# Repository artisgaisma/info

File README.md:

# Angle Meter 
### NO1 - BNO055 - Absolute Orientation Sensor- triaxial accelerometer, gyroscope, and magnetometer
```
Precise Orientation: The BNO055 is designed for precise orientation measurements and provides Euler angles (roll, pitch, and yaw) with three decimal places.
Integrated Sensor Fusion: The sensor fusion algorithm is implemented on the chip, reducing the complexity of fusion calculations on the microcontroller.
High Accuracy: The BNO055 is known for its high accuracy and low drift, making it suitable for applications that require precise orientation data.
Calibration: It includes an automatic calibration feature for both gyroscope and magnetometer, simplifying the calibration process.
Arduino Compatibility: There are Arduino libraries available for the BNO055, making it easy to use with Arduino projects.
```

### NO2 - MPU6050 - Inertial Measurement Unit (IMU) - accelerometer, gyroscope, and magnetometer
```which combines a 3-axis accelerometer and a 3-axis gyroscope.
While it doesn't have a built-in magnetometer, you can often integrate a
separate magnetometer module (like the HMC5883L or its successor, the QMC5883L) for better orientation accuracy
```

### NO3  - HMC5883L
```
is a three-axis digital compass module designed for low-field magnetic sensing with
a digital interface for applications such as compassing and magnetometry. It is
commonly used in electronic projects and devices where measuring the Earth's magnetic field is necessary.
```
###  ICM-20948 - most precise but better use BNO055
```
is designed to provide accurate readings of the Earth's magnetic field
it requires sensor fusion techniques. The ICM-20948 is a 9-axis sensor,
which means it includes a 3-axis accelerometer, a 3-axis gyroscope,
and a 3-axis magnetometer. By combining the data from these sensors and
applying sensor fusion algorithms, you can obtain accurate orientation
information, including roll, pitch, and yaw angles.
```

# Altitude

### NO1 - BMP388

# Other
- CDM -> diskpart -> list disk

# Restore
```
Solution #1: Restore Deleted Files from USB Drive Using CMD
1. Connect the USB flash drive to your computer.
2. Open the Start menu, type "cmd", and hit Enter on your keyboard.
3. Type "chkdsk X: /f" in the Command Prompt window and hit Enter. Just make sure to replace “X” with the letter assigned to your USB flash drive.recover deleted files from flash drive without software
4. Finally, type "ATTRIB -H -R -S /S /D X:*.*" and hit the Enter key (Again, replace “X” with the drive letter of the USB drive).recover deleted files from flash drive
5. Wait for the process to be completed.

Solution #2: Use the Restore Previous Versions Feature
1. Connect the USB flash drive to your computer.
2. Open the Start menu, type "This pc", and hit Enter on your keyboard.
3. Right-click on your USB flash drive and select "Properties".
4. Go to the "Previous Versions" tab and look at the list of available recovery options.
5. Select a previous version and click "Restore".

Solution #3: Use a Data Recovery Software 
Today we will be using the latest version of Disk Drill to recover data. It’s is one of the most popular and well-established data recovery software on the market.

Steps to recover deleted files from a USB flash drive:
1. Go to the following address and download Disk Drill: https://www.cleverfiles.com/
2. With your pen drive connected, launch Disk Drill 
3. Click the "Search for lost data" button next to it.
4. Select which files you want Disk Drill to recover and click the "Recover" button.
```

# MCU

`8MHZ - 8,000,000 cycles per second`

```int 4bytes -2`147`483`648	to 2`147`483`648 or uint32_t 4 bytes [0-4294967295]```

`EEPROM`	 write cycle typically takes 	`3.3 m`s to complete

## TI
		
|	|	I/O|		FLASH|	RAM|	BAND|
|----|----|----|----|----|
|CC1301	| 	10-30	|	32-128|	16/20|	Sub 1GHz, Wi-Fi|
|CC1350	|	10-33	|	128KB|	20KB|	Sub-1GHz, Wi-Fi, BLE|
|CC1352R|	28	|	352KB|	80KB|	Sub-1GHz AND 2.4GHz - DUAL BAND|
|CC1352P|	26	|	352KB|	80KB|	Sub-1GHz AND 2.4GHz - integrated amplifier|
|CC2640R2|	10-31	|	128KB|	20KB|	BLE 5, 2.4GHz|
|||||
||||
|CC110L| transmit|		<1.5e|	300-928MHz|
|CC115L| transmit|		<1e|	300-928MHz|
|CC1150| transmit|		<2e |	300-900MHz|
|CC1200| transceiv|		<2.5e| 	136-960MHz|
|CC1175| trannmit|		<2.5e |	136-960MHz| - 10pcs ordere - 25eur|

***CC1310 vs CC1350: Can be replacable each other.
The main advantage of the CC1352 over the CC1350 is the increased memory. 
With the increased memory you can run multiple stacks (TI15.4 and BLE). 
CC1350 can only run one stack at a time or one full stack and partially 
another for example, you can run the full TI 15.4 Stack with limited 
BLE functionality (only beaconing ad not connections)

### Atmel
```
		I/O 	FREQ	FLASH	EEPORM	RAM	PWM	USARTS
AVR128DA32		1-24	128KB	512B	16KB		3	has WatchDogTimer
Atmega 4808	27	1-20	48KB	256B	6KB	9	3	1.5
Atmega 4809	41	1-20	48KB	256B	6KB	11	4	1.5
Atmega 328p	23	1-20	32KB	1KB	2KB	6	1	1.5EUR
Atmega 32U4	26	8/16	32KB	1KB	2.5	5?	1
Atmega 1281 	54	8/16	128KB	4KB	8KB	6	2	6EUR
Atmega 2561	54	8/16	256KB	4KB	8KB	6	2
Atmega 1280	86	8/16	128KB	4KB	8KB	12	4
Atmega 2560	86	8/16	256KB	4KB	8KB	12	4
Atxmega256a3u 	64p	32	256	4KB	16KB	22	7	8eur	Allard QuadAnt taimeris

STM32F103x8	32	8-78	64KB	---	20KB	13	3	Have sample Board

SAMD21			48MHz	256KB	NO	32KB 12	

nRF52832
```
# Atmega BOD levels
- 4.3V - 100
- 2.7 - 101
- 1.8 - 110
- disabled -111
### Atmega4808/9
- MEgaCoreX - https://github.com/MCUdude/MegaCoreX
### BOD option
- Brownout detection or BOD for short lets the microcontroller sense the input voltage and shut down if the voltage goes below the brownout setting. Below is a table that shows the available BOD options:

### BOD threshold
4.3 V
4.0 V
3.7 V
3.3 V
2.9 V
2.6 V (default option)
2.1 V
1.8 V
Disabled
 
### LPC11U3x
32-bit ARM Cortex-M0 
up to 128 kB flash; 
upto 12 kB SRAM 
4 kB EEPROM
USB device
USART

## Ferrite Bead
```
A ferrite bead is a passive device that filters high frequency noise energy 
over a broad frequency range. It becomes resistive over its intended frequency
range and dissipates the noise energy in the form of heat. ... This forms
a low-pass filter network, further reducing the high frequency power supply noise.
```

## RT9193 - LDO with loadswitch

# CODE

### Data Types
```
	"32-bit CPU"
	char		1byte	-128				to 	127
	short		2bytes	-32`768 			to	32`768
	int		4bytes	-2`147`483`648			to	2`147`483`648
	long		4bytes	-2`147`483`648			to	2`147`483`648
	long long 	8bytes	-9`223`327`036`854`775`807 	to 	9`223`327`036`854`775`807
	float		4bytes	3.4E+/--38
	double		8bytes	1.7E+/--308
	long double	16bytes

	uint8_t		1 byte	[0-255]
	uint16_t	2 bytes	[0-65535]
	uint32_t	4 bytes	[0-4294967295]
	uint64_t	8 bytes	[0-18446744073709551615]
	
```

### Comparison
```
== (equal to)
!= (not equal to)
< (less than)
> (greater than)
<= (less than or equal to)
>= (greater than or equal to)
```
### Boolean Operators
```
! (logical not)
&& (logical and)
|| (logical or)
```

### Arithmetic
```
% (remainder)
* (multiplication)
+ (addition)
- (subtraction)
/ (division)
= (assignment operator)

y += x;	y = y + x;
x -= 5;	x = x - 5;
x /= y;	x = x / y;
```

### Compound Operators
```
&= (compound bitwise and)
*= (compound multiplication)
++ (increment)
+= (compound addition)
-- (decrement)
-= (compound subtraction)
/= (compound division)
^= (compound bitwise xor)
|= (compound bitwise or)
```

### Array
```
	array_1[] = array_2[] 	// tikai pieliidzina vienu elementu
	struct 1 = struct 2 	//pieliidzina visus elementus	
```
### Bitwise Operators
```
& (bitwise and)
<< (bitshift left)
>> (bitshift right)
^ (bitwise xor)
| (bitwise or)
~ (bitwise not)

	int a = 5;        // binary: 0000000000000101
	int b = a << 3;   // binary: 0000000000101000, or 40 in decimal
	int c = b >> 3;   // binary: 0000000000000101, or back to 5 like we started with

   	1 <<  0  ==    1
    	1 <<  1  ==    2
    	1 <<  2  ==    4
    	1 <<  3  ==    8
	
	int x = -16;     		// binary: 1111111111110000
 	int y = x >> 3;  		// binary: 1111111111111110
	int y = (unsigned int)x >> 3;	// binary: 0001111111111110

```
# Pointers
### print
```
void print(char* C){
	int i=0;		//var bez
	while(*(C+i)!= '/0'){ 	//var vnk C++
		printf("%c",C[i]);
		i++;//var C++
	}
	printf("/n");
}
int main(){
	char C[20] = "Hello";
	print(C);
}
```
### to Servos

```
107. rinda	#include <Servo.h>
			Servo STAB_SERVO;
			Servo WING_SERVO;
			Servo RUDD_SERVO;
			Servo HOOK_SERVO;
		/* MK edit - izveidojam poiteru matricu uz klasēm "ptr_Servo", kura glabajas objektu adreses */
		Servo* ptr_Servo[] = [ &STAB_SERVO, &WING_SERVO, &RUDD_SERVO, &HOOK_SERVO ];

203. rinda	void toParameters( uint8_t gID, uint8_t pID, float value ){
  
    			switch(gID){
        			case 1:
            				Parameters.FLY_TIME[pID] = value;
		/* MK edit - darbina servo */
		if ( pID > 4) ptr_Servo[PID]->write(value);

            				break;
				case 2:
            				Parameters.CIR[pID] = (uint8_t)value;
            				break;
```

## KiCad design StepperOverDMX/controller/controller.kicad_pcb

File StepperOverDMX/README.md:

# StepperOverDMX
A system to control a stepper motor over DMX protocol.

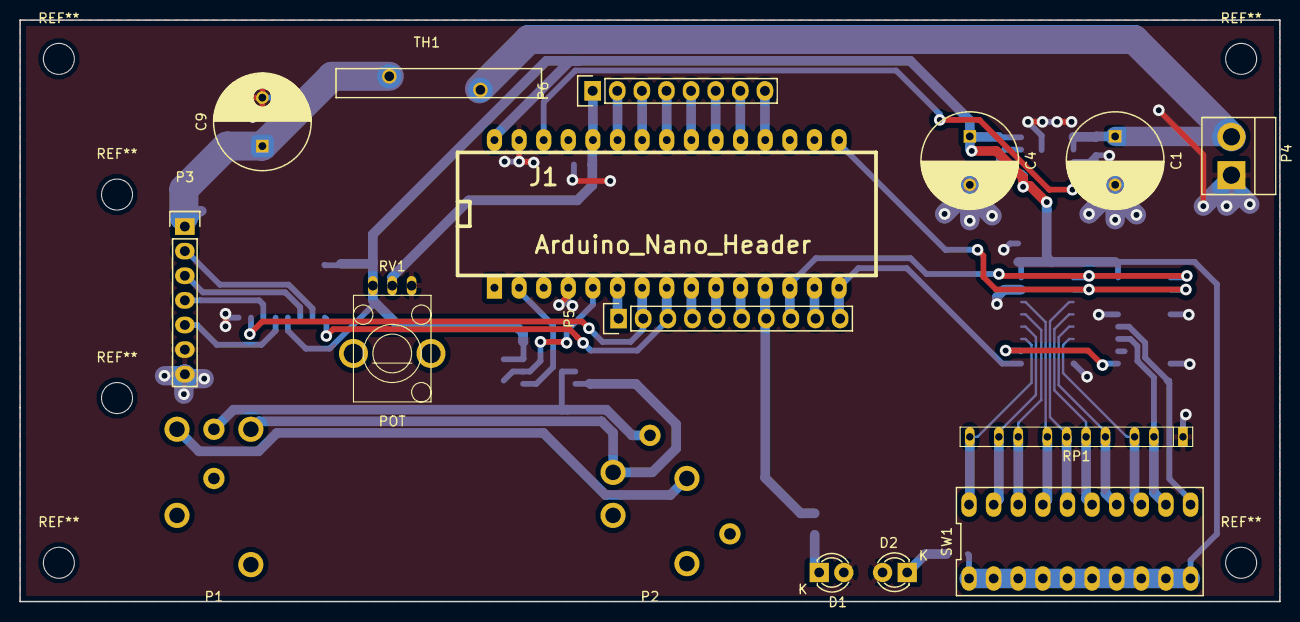
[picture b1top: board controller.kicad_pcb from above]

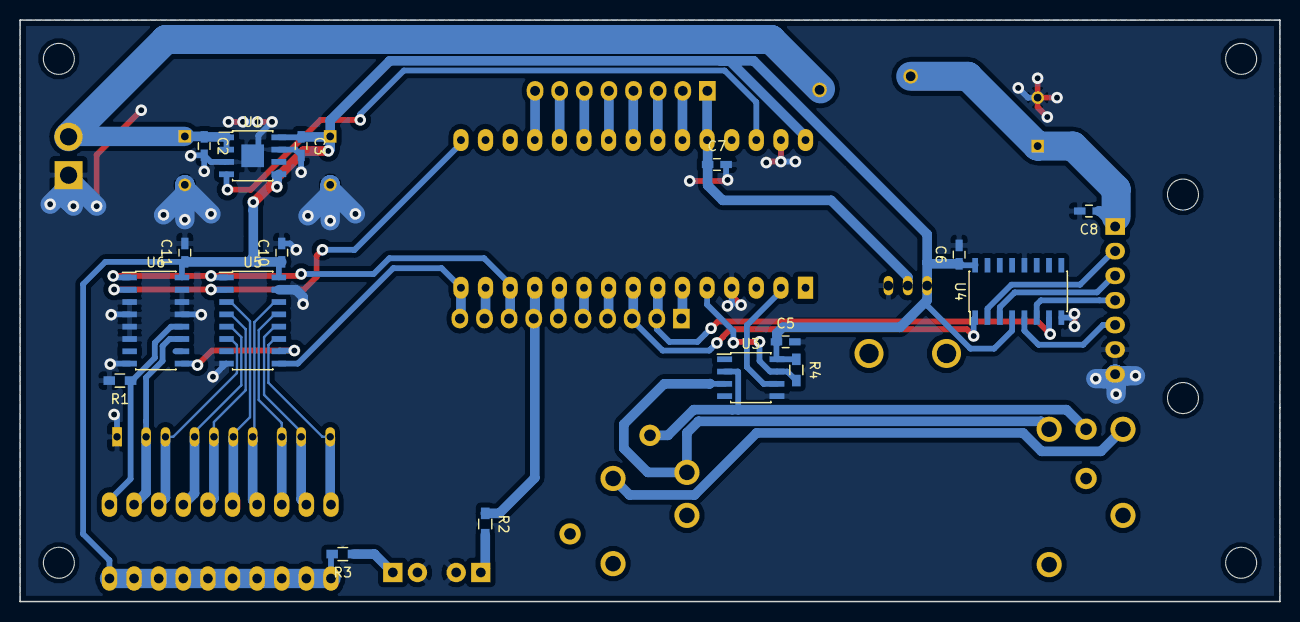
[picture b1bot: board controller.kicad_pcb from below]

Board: 2 copper layers, 130.0 x 60.0 mm, 33 parts (17 on the bottom side), 46 nets.

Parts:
C1, C4, C9: CP1; C_Radial_D10_L20_P5
C2, C3, C5, C6, C7, C8, C10, C11: 1u; C_0603_HandSoldering
D1, D2: LED; LED-3MM
J1: Arduino_Nano_Header; arduino_mini
P1: CONN_01X03; NC3MBH
P2: CONN_01X03; NC3FBH2
P3: CONN_01X07; Pin_Header_Straight_1x07
P4: CONN_01X02; Pin_Header_Straight_1x02_Pitch3.96mm_Friction_Lock
P5: CONN_01X10; Pin_Header_Straight_1x10
P6: CONN_01X08; Pin_Header_Straight_1x08
R1, R4: R; R_0603_HandSoldering
R2, R3: 330; R_0603_HandSoldering
RP1: R_PACK9_COMM; r-sil_10
RV1: POT; trimmer_alps-rk09k1130ah1
SW1: DIPS_10; A6ER-1010
TH1: THERMISTOR; MC36201
U1: MAX5024; SOIC-8-1EP_3.9x4.9mm_Pitch1.27mm
U3: IL610; SOIC-8_3.9x4.9mm_Pitch1.27mm
U4: MAX3040; SOIC-16_3.9x9.9mm_Pitch1.27mm
U5, U6: 74LS165; SOIC-16_3.9x9.9mm_Pitch1.27mm

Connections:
+5V: C3.1, C4.1, C5.1, C6.1, C10.1, C11.1, J1.30, R3.2, R4.1, RV1.3, SW1.1, SW1.2, SW1.3, SW1.4, SW1.5, SW1.6, SW1.7, SW1.8, SW1.9, SW1.10, U1.5, U1.8, U3.8, U4.4, U4.16, U5.16, U6.16
/CLOCK: J1.16, U5.2, U6.2
/DATA: J1.15, P5.10, U5.9
/DXM_OK: J1.12, P5.7, R2.1
/LATCH: J1.13, P5.8, U5.1, U6.1
/RESET: J1.28, U1.4
GND: C1.2, C2.2, C3.2, C4.2, C5.2, C6.2, C7.2, C8.2, C9.2, C10.2, C11.2, D1.2, D2.2, J1.4, J1.29, P3.6, P3.7, P4.1, R1.2, RP1.1, RV1.1, U1.3, U1.7, U1.9, U3.5, U4.8, U4.12, U5.8, U5.15, U6.3, U6.4, U6.5, U6.6, U6.8, U6.13, U6.14, U6.15
unnamed: C7.1, J1.26, P6.1, RV1.2
unnamed: C8.1, C9.1, P3.1, TH1.1
unnamed: D1.1, R2.2
unnamed: D2.1, R3.1
unnamed: J1.2, U3.6
unnamed: J1.5, R4.2, U3.7
unnamed: J1.6, P5.1
unnamed: J1.7, P5.2, U4.7
unnamed: J1.8, P5.3, U4.1
unnamed: J1.9, P5.4
unnamed: J1.10, P5.5
unnamed: J1.11, P5.6
unnamed: J1.14, P5.9
unnamed: J1.19, P6.8
unnamed: J1.20, P6.7
unnamed: J1.21, P6.6
unnamed: J1.22, P6.5
unnamed: J1.23, P6.4
unnamed: J1.24, P6.3
unnamed: J1.25, P6.2
unnamed: P1.1, P2.1
unnamed: P1.2, P2.2, U3.3
unnamed: P1.3, P2.3, U3.2
unnamed: P3.2, U4.2
unnamed: P3.3, U4.3
unnamed: P3.4, U4.6
unnamed: P3.5, U4.5
unnamed: R1.1, SW1.11, U6.12
unnamed: RP1.2, SW1.12, U6.11
unnamed: RP1.3, SW1.13, U5.6
unnamed: RP1.4, SW1.14, U5.5
unnamed: RP1.5, SW1.15, U5.4
unnamed: RP1.6, SW1.16, U5.3
unnamed: RP1.7, SW1.17, U5.14
unnamed: RP1.8, SW1.18, U5.13
unnamed: RP1.9, SW1.19, U5.12
unnamed: RP1.10, SW1.20, U5.11
unnamed: U5.10, U6.9
VCC: C1.1, C2.1, P4.2, TH1.2, U1.1, U1.2

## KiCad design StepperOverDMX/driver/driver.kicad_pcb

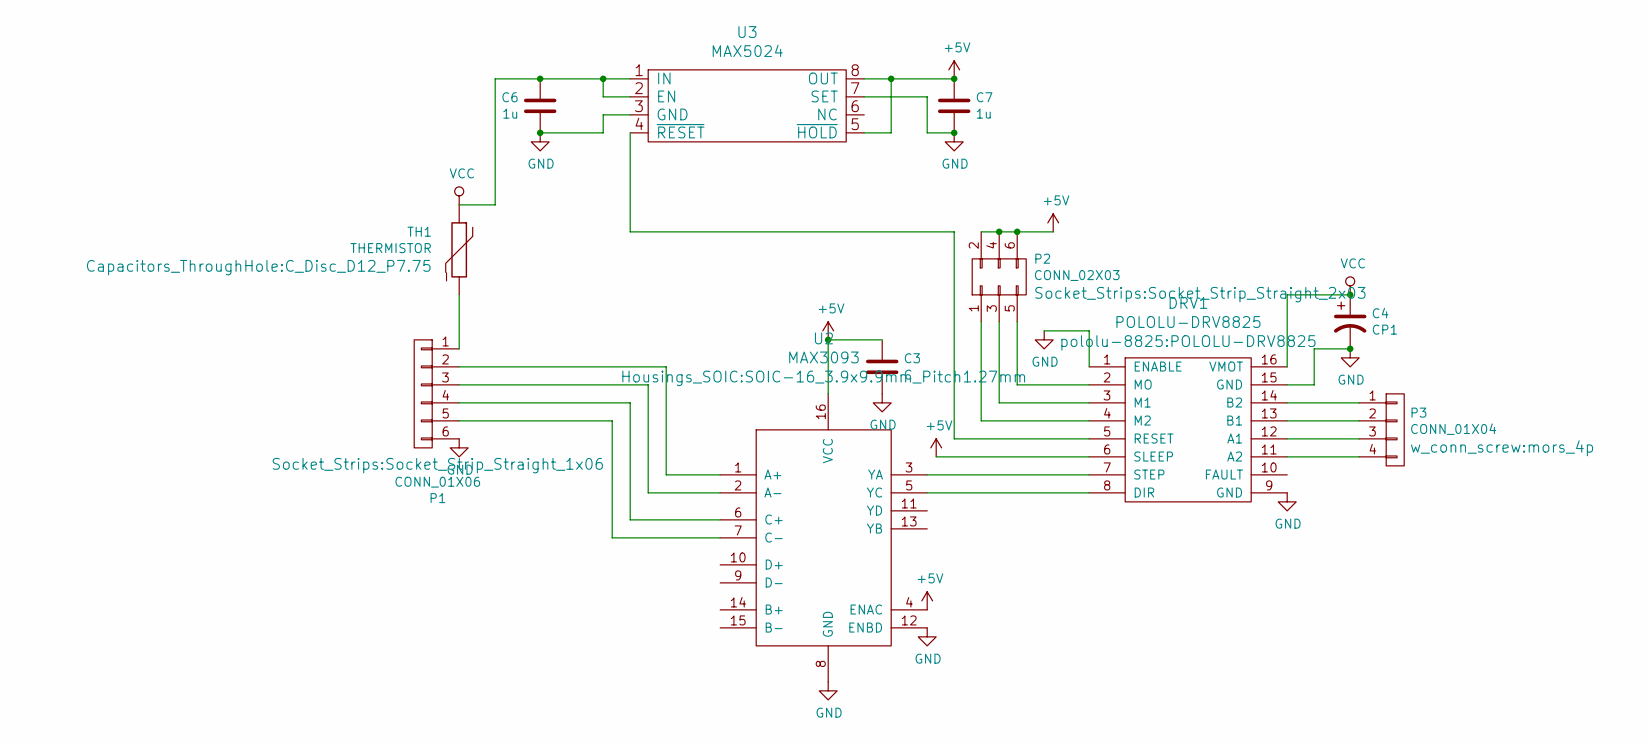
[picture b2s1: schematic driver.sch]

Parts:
C3: C; C_0603_HandSoldering
C4: CP1; C_Radial_D10_L20_P2.5
C6, C7: 1u; C_0603_HandSoldering
DRV1: POLOLU-DRV8825; PartNo ?
P1: CONN_01X06; Socket_Strip_Straight_1x06; PartNo ?
P2: CONN_02X03; Socket_Strip_Straight_2x03; PartNo ?
P3: CONN_01X04; mors_4p; PartNo ?
TH1: THERMISTOR; C_Disc_D12_P7.75; PartNo ?
U2: MAX3093; SOIC-16_3.9x9.9mm_Pitch1.27mm; PartNo ?
U3: MAX5024; SOIC-8-1EP_3.9x4.9mm_Pitch1.27mm; PartNo ?

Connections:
+5V: C3.1, C7.1, DRV1.6 (SLEEP), P2.2, P2.4, P2.6, U2.4 (ENAC), U2.16 (VCC), U3.5 (~HOLD), U3.8 (OUT)
GND: C3.2, C4.2, C6.2, C7.2, DRV1.1 (ENABLE), DRV1.9 (GND), DRV1.15 (GND), P1.6, U2.8 (GND), U2.12 (ENBD), U3.3 (GND), U3.7 (SET), U3.9
unnamed: DRV1.2 (MO), P2.5
unnamed: DRV1.3 (M1), P2.3
unnamed: DRV1.4 (M2), P2.1
unnamed: DRV1.5 (RESET), U3.4 (~RESET)
unnamed: DRV1.7 (STEP), U2.3 (YA)
unnamed: DRV1.8 (DIR), U2.5 (YC)
unnamed: DRV1.11 (A2), P3.4
unnamed: DRV1.12 (A1), P3.3
unnamed: DRV1.13 (B1), P3.2
unnamed: DRV1.14 (B2), P3.1
unnamed: P1.1, TH1.2
unnamed: P1.2, U2.1 (A+)
unnamed: P1.3, U2.2 (A-)
unnamed: P1.4, U2.6 (C+)
unnamed: P1.5, U2.7 (C-)
VCC: C4.1, C6.1, DRV1.16 (VMOT), TH1.1, U3.1 (IN), U3.2 (EN)

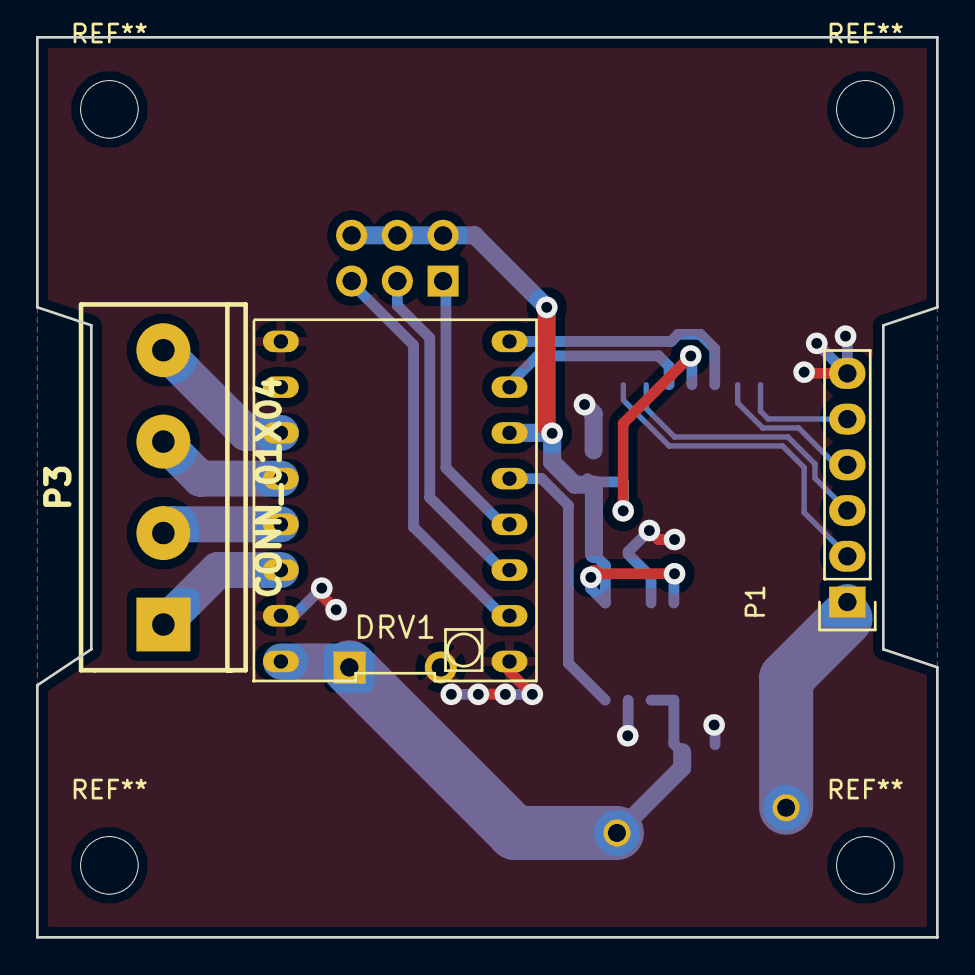
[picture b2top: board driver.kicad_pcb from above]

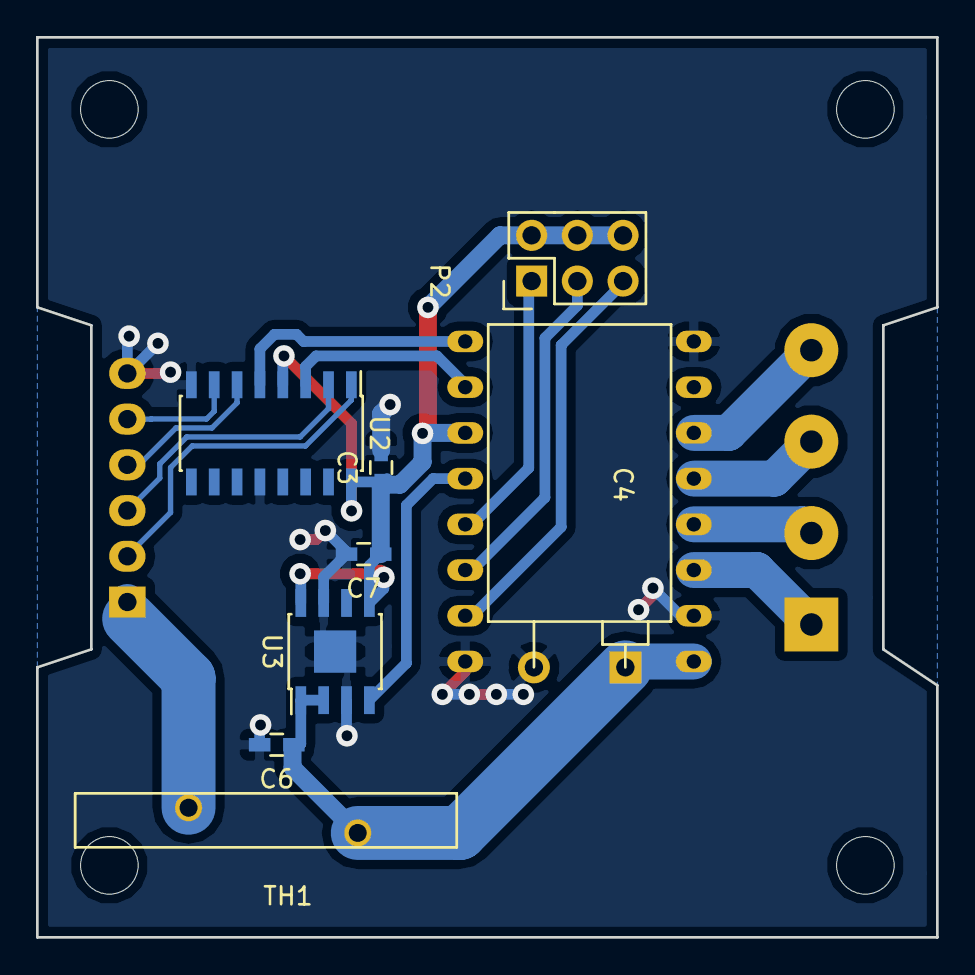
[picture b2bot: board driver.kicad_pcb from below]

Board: 2 copper layers, 50.0 x 50.0 mm, 11 parts (8 on the bottom side), 18 nets.

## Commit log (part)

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2021-11-10 add
    cc1352
    gps-rf
    hj-185
2021-11-10 update
    add info repos here
2021-11-25 rem
    unnecesary
2021-11-30 ADD
    MIC RF
2021-11-30 add
    micrf112
2021-11-30 add
    syn113/5
2021-12-13 add
    info about GPS form gps repo
2021-12-13 add
    rf info from GPS repo
2021-12-13 replace
    files
2021-12-13 Update README.md
    add library
2021-12-15 add
    parts pics
2021-12-20 add
    some info
2021-12-28 UPDATE
    CONNECTORS
2021-12-30 remove
    package directory to altium
2021-12-30 add
    more parts
2022-01-14 update
    new RF modules
2022-01-15 add
    l96
2022-01-15 add
    l96 specs
2022-01-22 add
    arduino libraries
2022-01-28 renam folder
2022-01-28 reaname
    parts doirectory
2022-01-28 update
    move files from MAC
2022-02-08 remove Softi
    directory
2022-02-08 rename
    fingerwing to dmx artnet
2022-03-03 add
    codes
2022-03-07 add
    artnet node arduino info
2022-05-21 add GPS view software
2022-05-31 update
    lcd librarys
2022-06-07 add
    sd card operations
2022-06-07 new directory for GPS softs
2022-06-08 reorder
2022-06-30 add
    DMX to OSC code
    adafruit gxf zip lib
2022-07-11 add
    LDO info
    code samples
2022-07-16 add
    pixel dmx artnet
2022-08-30 add
    info
2022-11-16 add
    LDO parts
2022-12-04 add
    dmx serial master
    parst info
    batt charger manual
2022-12-13 add
    ttl transceiver
2023-01-23 add
    LDO specs, mosfets, lora
2023-01-23 add
    loadswitches, n-fet info
2023-02-01 update
    parts library specs from flashka
2023-03-13 updade
    dade
2023-04-05 add
    boost mikrenes
2023-04-06 add
    mcu 4808 info
2023-05-07 bod level info
2023-12-13 update
    fasteled arduino
2023-12-18 add
    step down
2023-12-25 add
    flexible PCB sample
2024-01-24 add
    100n03 pdf n-mosfet
2024-01-25 reorganize
    mosfet and loadswitch
2024-01-25 rename
2024-02-09 add
    new parts
2024-02-14 Update README.md
    angle meter and altitude sensors
2024-02-15 add
    nrf52832 altium file
2024-02-17 add
    BLE antennas
2024-02-20 add
    atenna sample
2024-02-21 add
    ksc lan switch
2024-02-23 add
    rf rx tx modules
2024-03-28 add
    LAN vertical connector with traf
2024-11-10 add
    connectror info
2024-11-22 add
    led driwer
2025-01-22 add
    coneectors
2025-02-14 add
    step down hanrun
2025-02-15 add
    rj45 connector
2025-02-24 updatew
    rj45 connectors
2025-03-05 add
    reed switches
    mechanical switcher - micro
2025-04-04 add
    icsp prog pcb
2025-06-06 switches
2025-09-21 add
    oscillator specs
2025-10-08 add
    ic pixels
2025-11-06 update
    samsing
2025-11-18 replace
    specsheets
2025-11-30 new
    parts
2025-12-21 refresf
    directory clean
2025-12-21 add
    boost scheamatic
2026-01-05 add
    rectifier infos
2026-02-23 edit gitignore
2026-02-24 Update readme.txt with board manager links
    Added additional board manager URLs and updated tutorial link.
2026-03-22 add
    asmb didode
